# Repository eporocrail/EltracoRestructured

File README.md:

Aim is to develop a switching and signaling system for model railroad track control.
  Communication is wireless.

  To disconnect the decoder from the controlling software in space and time the MOSQUITTO
  MQTT broker is used.

  Hardware setup is as simple as possible. In stead of having one hardware module for diffferent applications
  the design aims for three different PCB's specific to task where the Wemos has to be slotted into.

  Sofware is modularised. It is gathered into one software package. The functionality of each separate decoder
  is configured by means of a website genrated by the decoder.

  *********************************************************************************************

  Target platform is Wemos D1 mini.

  11 digital input/output pins, all pins have interrupt/pwm/I2C/one-wire supported(except D0)
  1 analog input(3.2V max input)
  a Micro USB connection
  compatible with Arduino IDE.
  pins are active LOW but the Arduino IDE inverts this.

  All of the IO pins run at 3.3V:
  A levelshifter or voltage divider is required.

  For a relay a pin is followed by a transistor/IC. A relay is driven with 5V.

  For a sensor or servo each pin is followed by a 330R resistor to limit current to 10 mA.

  eltraco decoder     Function

  eltraco sensor decoder    Scanning 9 sensors
  eltraco switch decoder    Controlling 8 outputs
  eltraco turnout decoder   Controlling 2 turnouts

  GPIO usage:

  Decoder  pins     function

  Sensor   D0 .. D7     digital sensor
  
           A0           analogue sensor

  Switch   D0 .. D7     output (switch)

  Double   D0    relais 1
  
  Turnout  D1    current detector 1
           
           D2    current detector 2
           
           D3    not used
           
           D4    not used
           
           D5    relais 2
           
           D6    servo 1
           
           D7    servo 2
           
           D8    not used
           
           A0    not used
           
  Single   D0    relais 1
  
  Turnout  D1    current detector 1
           
           D2    sensor
           
           D3    sensor
           
           D4    sensor
           
           D5    sensor
           
           D6    servo 1
           
           D7    not used
           
           D8    not used
           
           A0    not used         

  ROCNET PROTOCOL

  packet payload content:
  byte 1  : groupId
  
  byte 2  : receiveIdH
  
  byte 3  : receiveIdL
  
  byte 4  : sendIdH
  
  byte 5  : sendIdL
  
  byte 6  : group
  
  byte 7  : code
  
  byte 8  : length
  
  byte 9  : data1
  
  byte 10 : data2
  
  byte 11 : data3
  
  byte 12 : data4

  --byte 1 only used for large network. Normally 0.

  --byte 2 only used when more than 255 decoders. Normally 0.

  --byte 3 Rocrail Server default Id is 1

  Broadcast Id = 0
  
  Decoder   Id = 2 ... 255   Not used for switching decoder

  --byte 4 only used when more than 255 decoders. Normally 0.

  --byte 5 Rocrail Server default Id is 1

  Decoder Id   = 2 ... 255 with restrictions as described under "addressing"

  --byte 6

  groups
  code   description     remark                     MQTT topic
  
  0      Host            Rocrail                    rocnet/ht
  
  7      Clock Fast      Clock                      rocnet/ck
  
  8      Sensor          Position determination     rocnet/sr
  
  9      Output                                     rocnet/ot

  --byte 7

  Code:  bit 7 = 0
  
     bit 6 and bit 5 represent Type of code
     
     bit 4 .. 0:  5 bit command 0 .. 31

  Type: 0 - test
  
  1 - request
  
  2 - event
  
  3 - reply

  Sensor

  Actions
  code description data 1  data 2  data 3  data 4  data n
  1    report      addrH¹  addrL¹  status  port    identifier (RFID)

  ¹) Address of the reporting loco.
  The sensor ID is set in the header; Sender.

  Output

  Type   Value
  
  switch   0
  
  light    1
  
  servo    2

  Actions
  code description data 1  data 2  data 3
  
  0      off       type    value   address
  
  1      on        type    value   address

  --byte 8 Netto number of following data bytes.

  At a speed of 200 KmH a loc runs 64 mm per second in scale H0 and 35 mm per second in scale N.
  To come to a reliable detection reaction a point sensor must be scanned at least 20 times per second in H0
  and at least 10 times per second in scale N.

  For scale H0 scan delay should be not larger than 50 miliseconds and for scale N not larger
  than 100 miliseconds. Default will be 20.

  The Wemos Module needs no 3.3V power supply. To the 5V pin external powersupply can be connected.

  Addressing:

  Addressing falls apart in a WiFi address, being an IP-address and a Rocnet address.

  Rocnet:

  In the Rocnet protocol (IdH*256 + IdL) represents the Rocnet Node Number. This number ranges from 1 .. 65536.
  It represents the "Bus" number.
  Depending on the function performed the I/O pin of the decoder is addressed with "data3" for
  "output" functions or "data4" for "sensor" functions. Turnouts are controlled with an "output" function.
  The values of data3/data4 are in rocrail inserted in field "Address"

  For eltraco an I/O pin is addressed by the combination of receiveIdL and data3/data4.
  This way each individual pin of each individual decoder can be addressed.

  A second way to address an IO pin is using a "fixed" receiveIdL and discriminating by means of data3/data4.
  Using this method provides in eltraco the possibility to address 255 turnouts by a consecutive number only.
  The default receiveIdL of Rocrail is "9". This receiveIdL is used to control turnouts. These addresses are
  used by the servo-tool to adjust the servo of a turnout.

  IP-address:
  The following IP-adress range is available:
  192.168.xxx.xxx

  IP-addres: Router 192.168.xxx.251
  
             Configuration website 192.168.xxx.252
             
             Command Station       192.168.xxx.253
             
             Mosquitto             192.168.xxx.254

  For the decoders are available 192.168.xxx.2 - 192.168.2.250

  Each decoder is allocated a unique IP-address out of the range 192.168.xxx.2 - 192.168.2.250.
  The last triplet is the Rocrail "Bus" number.

  Single turnout decoder:

Each decoder controls 1 turnout and reports occupation of it.

For the turnout decoder occupation of the turnout is reported at "Address" 1.

Table: Switches tab Interface - the last part of the IP-address is inserted into field "Bus"
       "1" is inserted into field "Address".
       e.g. (192.168.0.154 turnout is inserted as Bus 154 Address 1)

Table: Sensor tab Interface - the last part of the IP-address is inserted into field "Bus"
       "1" is inserted into field "Address". The external sensors report using "Address" numbers 2 .. 5.
       e.g. (192.168.0.154 turnout is inserted as Bus 154 Address 1, the second external sensor of the same
       decoder is inserted as Bus 154 Address 3)

Double turnout decoder:

Each decoder controls 2 turnouts and reports occupation of them.

For the turnout decoder occupation of the first turnout is reported at "Address" 1 and of the second
turnout at "Address" 2.

Table: Switches tab Interface - the last part of the IP-address is inserted into field "Bus"
       For the first turnout "1" is inserted into field "Address". For the second one "2" is inserted
       e.g. (192.168.0.154 turnout 2 is inserted as Bus 154 Address 2)

Table: Sensor tab Interface - the last part of the IP-address is inserted into field "Bus"
       For the first turnout "1" is inserted into field "Address". For the second one "2" is inserted
       e.g. (192.168.0.154 turnout 2 is inserted as Bus 154 Address 2)

Operation

During testing it turned out that move orders from Rocrail arrived so fast that an ongoing movement was
interrupted. To cater for this, incoming turnout orders are stored into a buffer. When ongoing movement is concluded,
buffer content is converted into a turnout order and the next turnout starts moving.

Sensor decoder:
Each decoder has eight digital and one analogue sensor.

The sensors report using "Address" numbers 1 .. 9.
Use of the analogue sensor is to be programmed by the user.

Table: Sensor tab Interface - the last part of the IP-address is inserted into field "Bus"
       port number is inserted into field "Address"
       e.g. (192.168.0.076 sensor 5 is inserted as Bus 76 Address 5)

Operation

The state of the sensor is controlled by interrupt. Not only the state of the sensor but also the point in time of activation is stored.
If the sensor is still in the activated state after the debounce period has passed the Sensor Message is sent. 

The state of the sensor will change to "inactive" by interrupt. After the minimum activation time has passed this inactive state is signalled 

The state of the sensor will change to "inactive" by interrupt. After the minimum activation counts has passed this inactive state is signalled 

with a Sensor Message.

Interrupt reacts on changes to drive the sensor state.

D0 can NOT be used with Interrupt. This reduces the amount of interrupt driven sensors per module to 7. (D1 .. D7).

D0 has to be watched with "polling".

Switch decoder
Each decoder has eight outputs.

Each decoder is allocated a unique IP-address out of the range 192.168.xxx.2 - 192.168.2.250.
The last triplet is the Rocrail "Bus" number.

The outputs are switched using "Address" numbers 1 .. 8.

Table: Switches tab Interface - the last part of the IP-address is inserted into field "Bus"
       The individual port number is inserted into field "Address"
       e.g. (192.168.0.201 port 3 is inserted as Bus 201 Address 3)

Operation

Via configuration it is possible to have an output switched ON during 200 mSec. An additional relais attached to that
output can be used to control a solenoid activated device.

To signal the state of a switch, a sensor message is transmitted after each switch action. 

Configuration of decoder

The Wemos module can be used in "ST" mode and "AP" mode simultaneously.
In "ST" mode it is possible to login onto an existing WiFi network for normal operations.
In "AP" mode it is possible to generate its own WiFi network. This network is used for configuration of the decoder.
Each module has its own configuration webserver on a shared WiFi configuration network with its own IP address.

The websever is based on the "EmbAJAX" library. This library facilitates dataexchange between webserver on the decoder
and a browser on a client. The user experience is as much as possible comparable with webservers on PC like hardware.

Configuration data and servo angles are stored in EEPROM.
Allocation of EEPROM memory to variables has to be planned.
  location variable
      0    AngleA1
      1    AngleB1
      2    Delay1
      3    Swap1
      4    AngleA2
      5    AngleB2
      6    Delay2
      7    Swap2
      8    decoderType
      9    debugFlag

  GENERALOFFSET+ 0 .. 25 ST WiFi SSID
  
  GENERALOFFSET + SSIDOFFSET + 0 .. 8 ST WiFi Password
  
  GENERALOFFSET + SSIDOFFSET + PWDOFFSET + 0 .. 6 ST WiFi IP address triplets
  
  GENERALOFFSET + SSIDOFFSET + PWDOFFSET + IPOFFSET + 0 .. 8 Output puls 
  
  GENERALOFFSET + SSIDOFFSET + PWDOFFSET + IPOFFSET + OUTPUTOFFSET + 0 .. 8 Switch active puls length

Configuration data and servo angles are stored in EEPROM.
Allocation of EEPROM memory to variables has to be planned.
  location variable
      0    AngleA1
      1    AngleB1
      2    Delay1
      3 .  Swap1
      4    AngleA2
      5    AngleB2
      6    Delay2
      7 .  Swap2
      8    decoderType
      9    debugFlag

  GENERALOFFSET+ 0 .. 25 ST WiFi SSID
  
  GENERALOFFSET + SSIDOFFSET + 0 .. 8 ST WiFi Password
  
  GENERALOFFSET + SSIDOFFSET + PWDOFFSET `+ 0 .. 6 ST WiFi IP address triplets
  
  GENERALOFFSET + SSIDOFFSET + PWDOFFSET + IPOFFSET + 0 .. 8 Output puls 
  
  GENERALOFFSET + SSIDOFFSET + PWDOFFSET + IPOFFSET + OUTPUTOFFSET + 0 .. 8 Switch active puls length 
  
  GENERALOFFSET + SSIDOFFSET + PWDOFFSET + IPOFFSET + OUTPUTOFFSET + PULSLENGTHOFFSET+ 0 .. 8 Output sensor message

  GENERALOFFSET      - 20
  SSIDOFFSET         - 30
  PWDOFFSET          - 20
  IPOFFSET           - 10
  OUTPUTOFFSET        -10
  PULSLENGTHOFFSET    -20
  OUTPUTSENSOROFFSET  -10

The ST WiFi password is generated out of "ELTRACO" and the decoderId.
The AP WiFi SSID is generated out of "ELTRACO" and the decoderID. This also aplies to the related password.

There are two ways to transfer Software to the decoder.
Via USB cable and after inital software installation also "Over The Air"(OTA).
Each decoder has its own OTA name which is generated outof "ELTRACO" and the decoderId.

Author: E. Postma

November 2018

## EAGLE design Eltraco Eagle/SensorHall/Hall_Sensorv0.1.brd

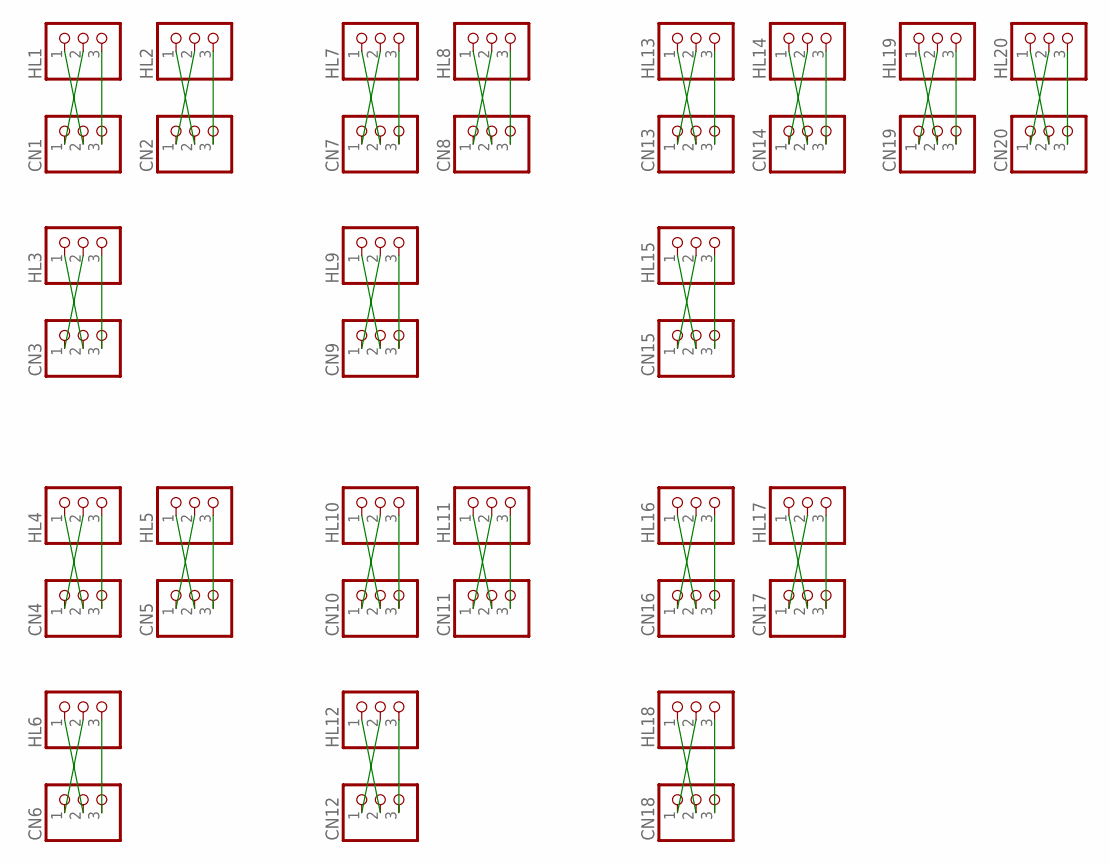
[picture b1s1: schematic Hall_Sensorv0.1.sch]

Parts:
CN1, CN2, CN3, CN4, CN5, CN6, CN7, CN8, CN9, CN10, CN11, CN12, CN13, CN14, CN15, CN16, CN17, CN18, CN19, CN20: PINHD-1X3; 1X03
HL1, HL2, HL3, HL4, HL5, HL6, HL7, HL8, HL9, HL10, HL11, HL12, HL13, HL14, HL15, HL16, HL17, HL18, HL19, HL20: PINHD-1X3; 1X03

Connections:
unnamed: CN1.1, HL1.2
unnamed: CN1.2, HL1.1
unnamed: CN7.3, HL7.3
unnamed: CN2.2, HL2.1
unnamed: CN2.1, HL2.2
unnamed: CN8.3, HL8.3
unnamed: CN7.2, HL7.1
unnamed: CN7.1, HL7.2
unnamed: CN9.3, HL9.3
unnamed: CN8.2, HL8.1
unnamed: CN8.1, HL8.2
unnamed: CN10.3, HL10.3
unnamed: CN13.2, HL13.1
unnamed: CN13.1, HL13.2
unnamed: CN11.3, HL11.3
unnamed: CN14.2, HL14.1
unnamed: CN14.1, HL14.2
unnamed: CN12.3, HL12.3
unnamed: CN19.2, HL19.1
unnamed: CN19.1, HL19.2
unnamed: CN13.3, HL13.3
unnamed: CN20.2, HL20.1
unnamed: CN20.1, HL20.2
unnamed: CN14.3, HL14.3
unnamed: CN15.2, HL15.1
unnamed: CN15.1, HL15.2
unnamed: CN15.3, HL15.3
unnamed: CN9.2, HL9.1
unnamed: CN9.1, HL9.2
unnamed: CN16.3, HL16.3
unnamed: CN3.2, HL3.1
unnamed: CN3.1, HL3.2
unnamed: CN17.3, HL17.3
unnamed: CN4.2, HL4.1
unnamed: CN4.1, HL4.2
unnamed: CN18.3, HL18.3
unnamed: CN5.2, HL5.1
unnamed: CN5.1, HL5.2
unnamed: CN19.3, HL19.3
unnamed: CN10.2, HL10.1
unnamed: CN10.1, HL10.2
unnamed: CN11.2, HL11.1
unnamed: CN20.3, HL20.3
unnamed: CN11.1, HL11.2
unnamed: CN1.3, HL1.3
unnamed: CN16.2, HL16.1
unnamed: CN16.1, HL16.2
unnamed: CN17.2, HL17.1
unnamed: CN17.1, HL17.2
unnamed: CN6.2, HL6.1
unnamed: CN2.3, HL2.3
unnamed: CN6.1, HL6.2
unnamed: CN12.2, HL12.1
unnamed: CN12.1, HL12.2
unnamed: CN3.3, HL3.3
unnamed: CN18.2, HL18.1
unnamed: CN18.1, HL18.2
unnamed: CN4.3, HL4.3
unnamed: CN5.3, HL5.3
unnamed: CN6.3, HL6.3

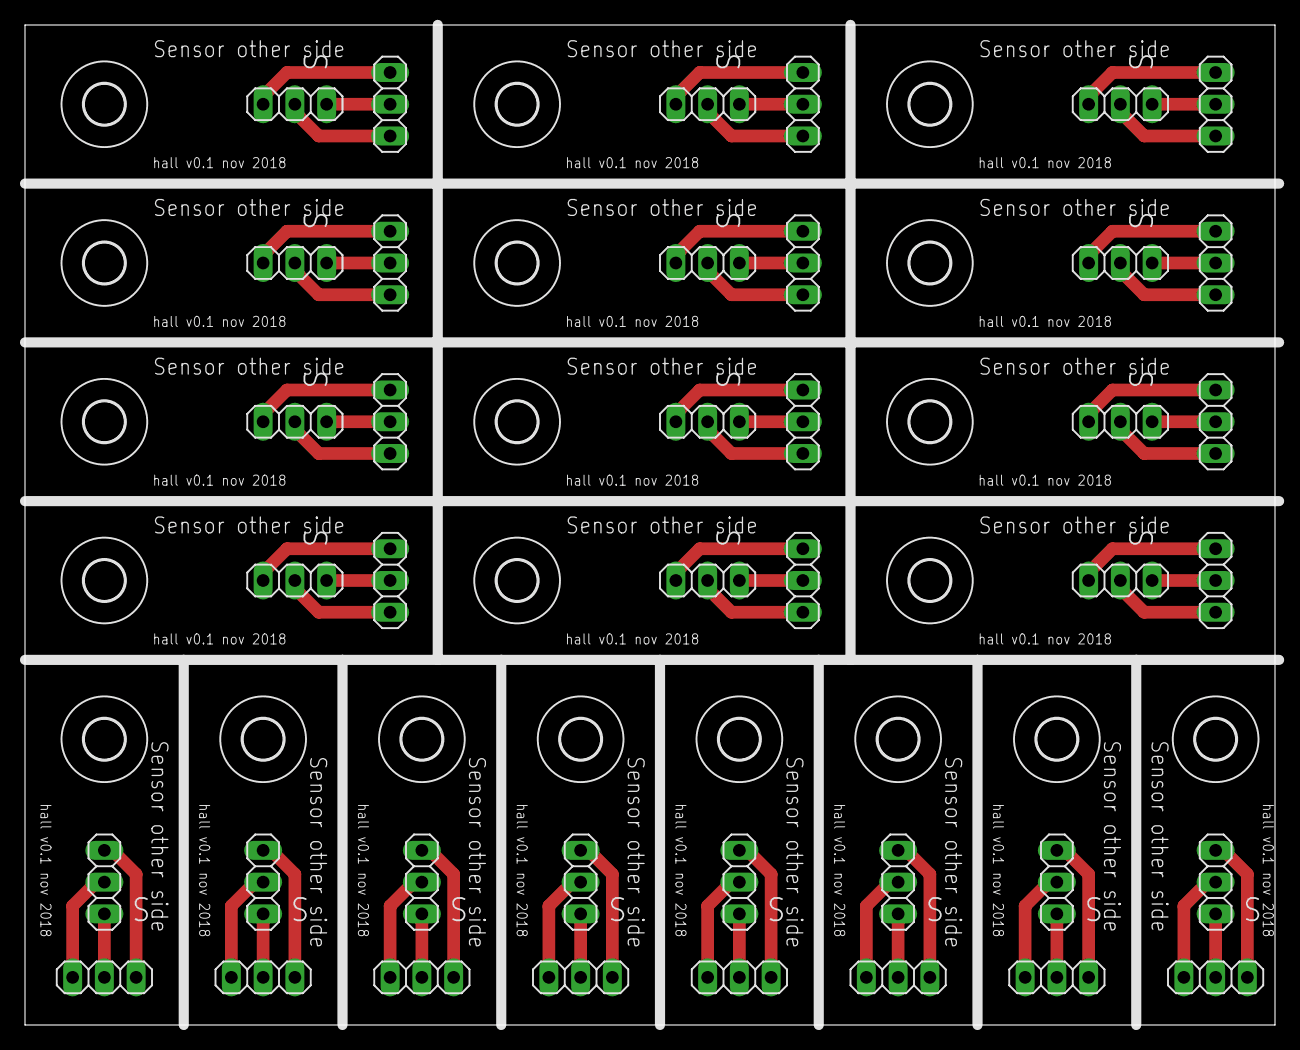
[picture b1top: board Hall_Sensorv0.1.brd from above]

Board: 2 copper layers, 100.0 x 80.0 mm, 60 parts (0 on the bottom side), 60 nets.

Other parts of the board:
U$1, U$2, U$3, U$4, U$5, U$6, U$7, U$8, U$9, U$10, U$11, U$12, U$13, U$14, U$15, U$16, U$17, U$18, U$19, U$20: 3,2

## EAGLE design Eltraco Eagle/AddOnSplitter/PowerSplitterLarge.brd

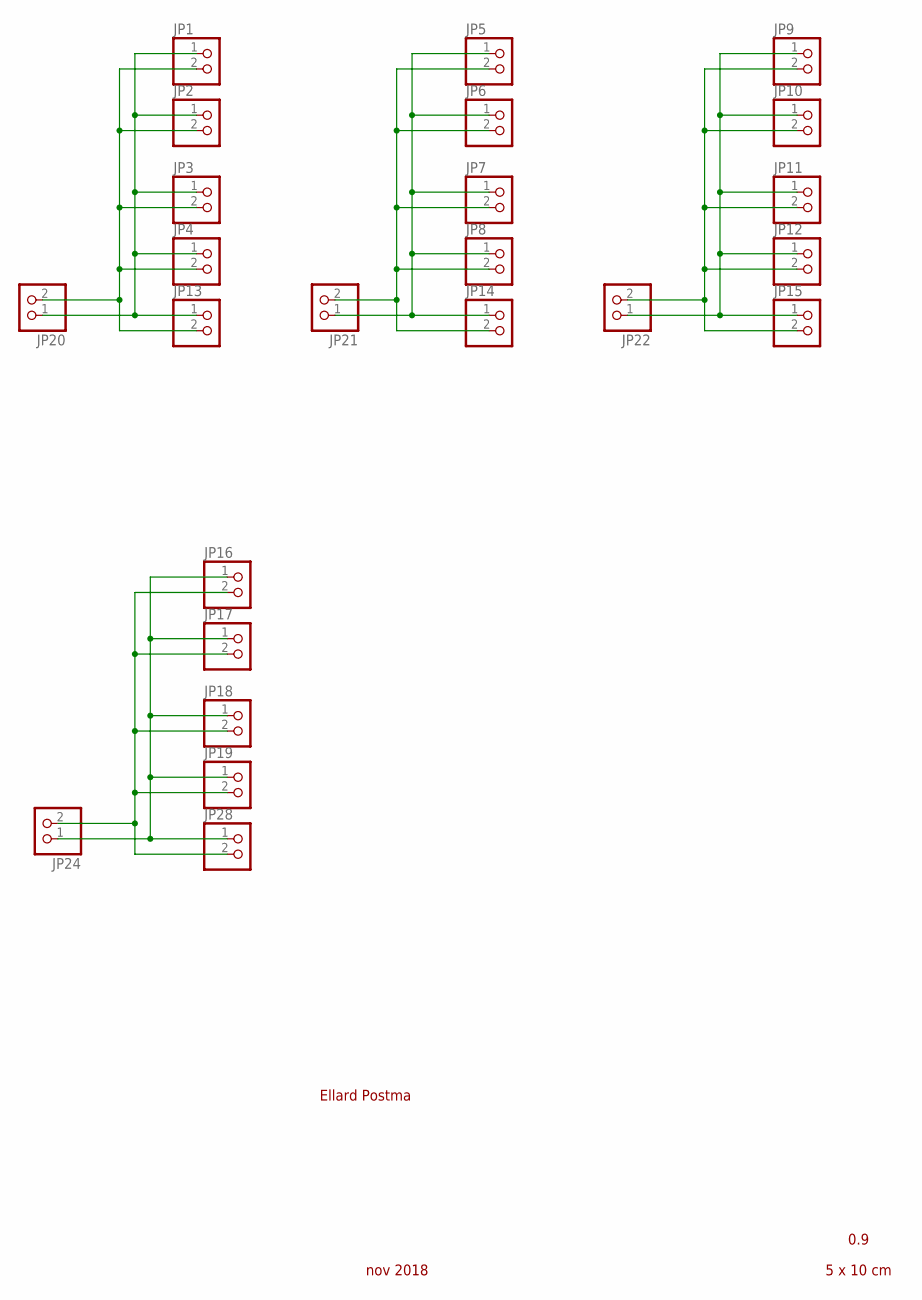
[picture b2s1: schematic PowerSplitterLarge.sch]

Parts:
JP1, JP2, JP3, JP4, JP5, JP6, JP7, JP8, JP9, JP10, JP11, JP12, JP13, JP14, JP15, JP16, JP17, JP18, JP19, JP20, JP21, JP22, JP24, JP28: PINHD-1X2/90; 1X02/90

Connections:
G1: JP1.2, JP2.2, JP3.2, JP4.2, JP13.2, JP20.2
G2: JP5.2, JP6.2, JP7.2, JP8.2, JP14.2, JP21.2
G3: JP9.2, JP10.2, JP11.2, JP12.2, JP15.2, JP22.2
G4: JP16.2, JP17.2, JP18.2, JP19.2, JP24.2, JP28.2
PLUS: JP1.1, JP2.1, JP3.1, JP4.1, JP13.1, JP20.1
PLUS2: JP5.1, JP6.1, JP7.1, JP8.1, JP14.1, JP21.1
PLUS3: JP9.1, JP10.1, JP11.1, JP12.1, JP15.1, JP22.1
PLUS4: JP16.1, JP17.1, JP18.1, JP19.1, JP24.1, JP28.1

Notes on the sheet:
Ellard Postma
nov 2018
5 x 10 cm
0.9

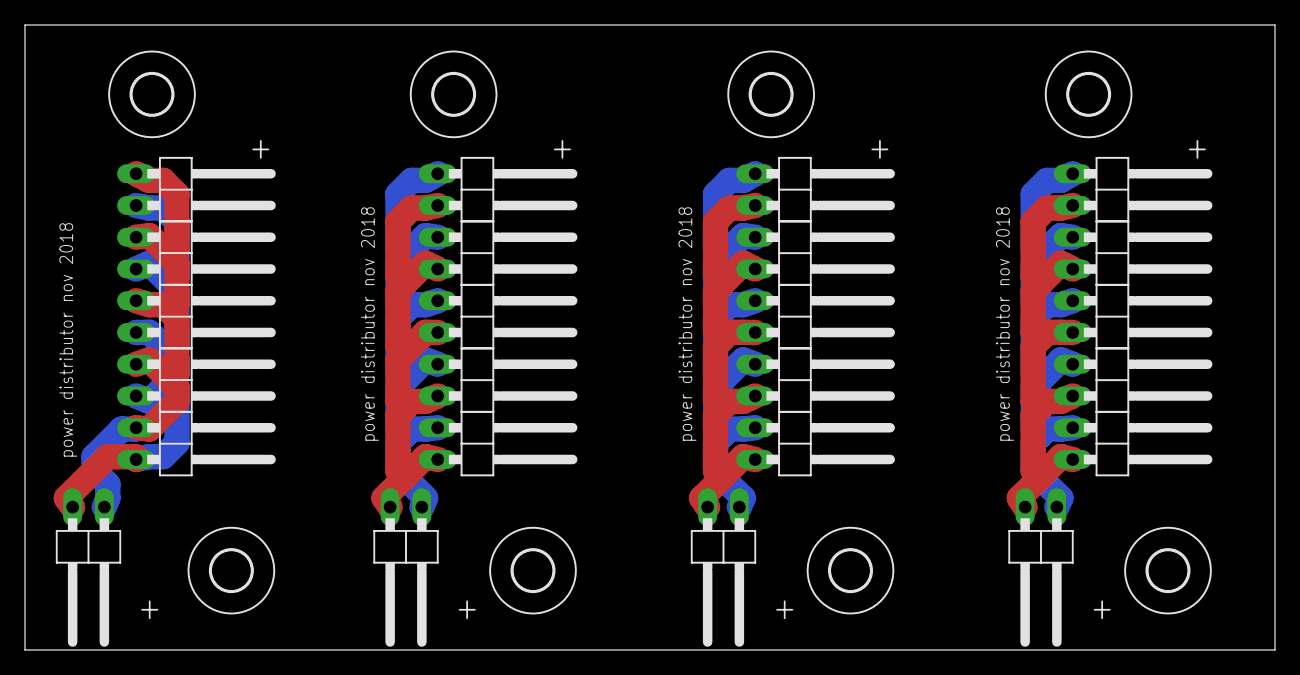
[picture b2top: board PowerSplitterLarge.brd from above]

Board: 2 copper layers, 100.0 x 50.0 mm, 32 parts (0 on the bottom side), 8 nets.

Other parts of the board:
U$1, U$2, U$3, U$4, U$5, U$6, U$7, U$8: 3,2

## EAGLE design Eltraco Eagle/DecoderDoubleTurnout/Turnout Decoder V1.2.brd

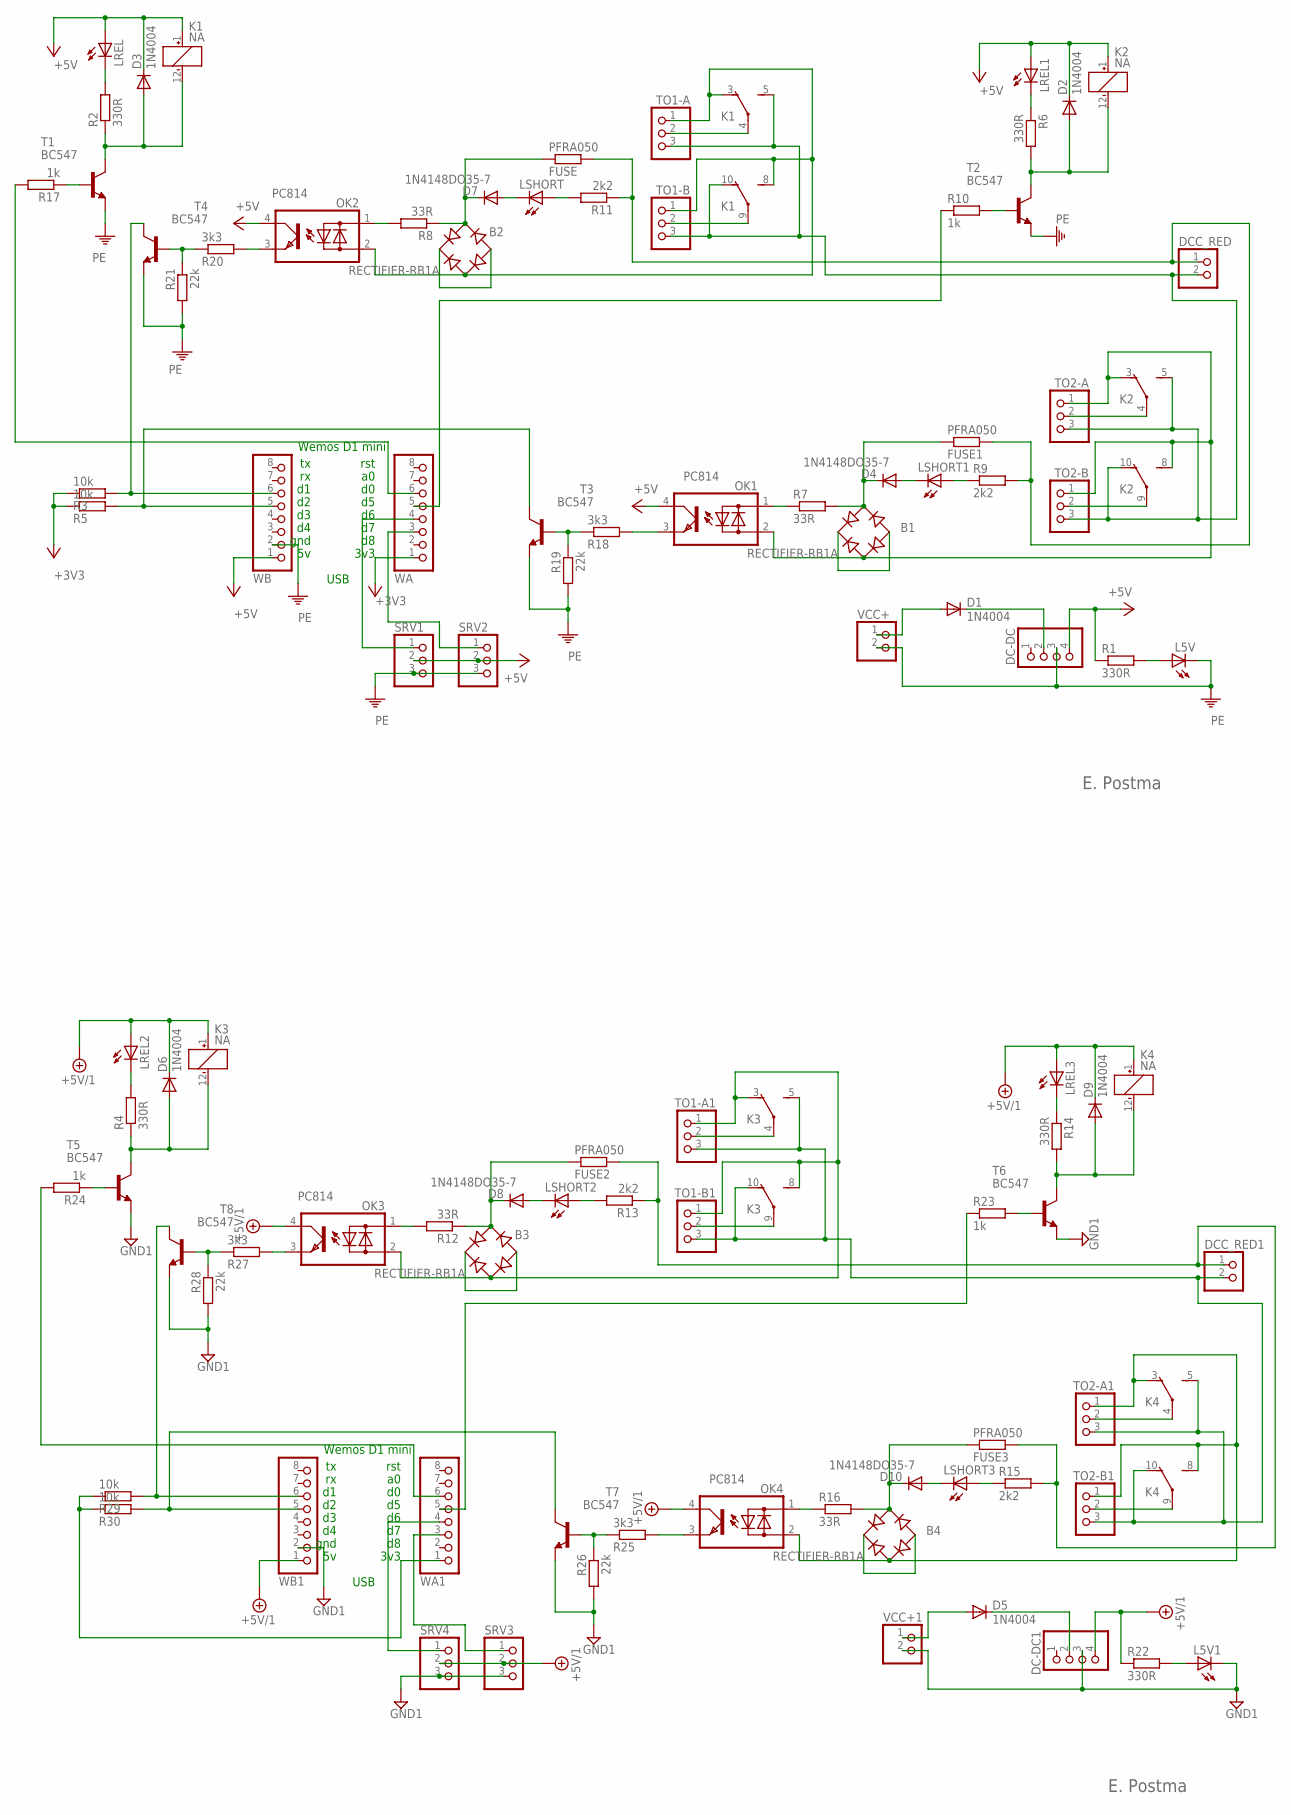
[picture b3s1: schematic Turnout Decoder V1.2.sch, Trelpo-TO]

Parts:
B1, B2, B3, B4: RECTIFIER-RB1A; RB1A
D1, D2, D3, D5, D6, D9: 1N4004; DO41-10
D4, D7, D8, D10: 1N4148DO35-7; DO35-7
DC-DC, DC-DC1: PINHD-1X4; 1X04
DCC_RED, DCC_RED1: PINHD-1X2; 1X02
FUSE, FUSE1, FUSE2, FUSE3: PFRA050; 0414V
K1, K2, K3, K4: NA
L5V, L5V1: LED3MM
LREL, LREL1, LREL2, LREL3: LED3MM
LSHORT, LSHORT1, LSHORT2, LSHORT3: LED3MM
OK1, OK2, OK3, OK4: PC814; DIL04
R1, R2, R4, R6, R14, R22: 330R; 0207/7
R3, R5, R29, R30: 10k; 0207/7
R7, R8, R12, R16: 33R; 0207/7
R9, R11, R13, R15: 2k2; 0207/7
R10, R17, R23, R24: 1k; 0207/7
R18, R20, R25, R27: 3k3; 0207/7
R19, R21, R26, R28: 22k; 0207/7
SRV1, SRV2, SRV3, SRV4: PINHD-1X3; 1X03
T1, T2, T3, T4, T5, T6, T7, T8: BC547; TO92
TO1-A, TO1-A1, TO1-B, TO1-B1, TO2-A, TO2-A1, TO2-B, TO2-B1: PINHD-1X3; 1X03
VCC+, VCC+1: PINHD-1X2; 1X02
WA, WA1: PINHD-1X8; 1X08
WB, WB1: PINHD-1X8; 1X08

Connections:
+3V3: R3.1, R5.1, WA.1
+5V: D2.C, D3.C, DC-DC.4, K1.1 (+), K2.1 (+), LREL.A, LREL1.A, OK1.4 (C), OK2.4 (C), R1.1, SRV1.2, SRV2.2, WB.1
+5V/1: D6.C, D9.C, DC-DC1.4, K3.1 (+), K4.1 (+), LREL2.A, LREL3.A, OK3.4 (C), OK4.4 (C), R22.1, SRV3.2, SRV4.2, WB1.1
GND1: DC-DC1.3, L5V1.K (C), R26.2, R28.2, SRV3.3, SRV4.3, T5.1 (E), T6.1 (E), T7.1 (E), T8.1 (E), VCC+1.2, WB1.2
unnamed: LREL2.K (C), R4.2
unnamed: LREL1.K (C), R6.1
unnamed: DCC_RED.1, FUSE.2, FUSE1.2, R9.2, R11.1
unnamed: D1.A, VCC+.1
unnamed: OK1.1 (AC1), R7.1
unnamed: LSHORT1.A, R9.1
unnamed: D4.A, LSHORT1.K (C)
unnamed: D2.A, K2.12 (-), R6.2, T2.3 (C)
unnamed: R10.2, T2.2 (B)
unnamed: B1.+, B1.-
unnamed: OK1.3 (E), R18.2
unnamed: LREL.K (C), R2.2
unnamed: K2.4, TO2-A.2
unnamed: B2.AC2, K1.3 (O), K1.8 (S), OK2.2 (AC2), TO1-A.1, TO1-B.1
unnamed: K2.9, TO2-B.2
unnamed: DCC_RED.2, K1.5 (S), K1.10 (O), K2.5 (S), K2.10 (O), TO1-A.3, TO1-B.3, TO2-A.3, TO2-B.3
unnamed: OK2.3 (E), R20.2
unnamed: B1.AC2, K2.3 (O), K2.8 (S), OK1.2 (AC2), TO2-A.1, TO2-B.1
unnamed: R3.2, T4.3 (C), WB.6
unnamed: B1.AC1, D4.C, FUSE1.1, R7.2
unnamed: OK2.1 (AC1), R8.2
unnamed: R5.2, T3.3 (C), WB.5
unnamed: B2.AC1, D7.C, FUSE.1, R8.1
unnamed: OK3.1 (AC1), R12.2
unnamed: LSHORT2.A, R13.2
unnamed: K1.4, TO1-A.2
unnamed: R18.1, R19.1, T3.2 (B)
unnamed: R20.1, R21.1, T4.2 (B)
unnamed: R17.2, WA.6
unnamed: D8.A, LSHORT2.K (C)
unnamed: SRV1.1, WA.4
unnamed: K1.9, TO1-B.2
unnamed: SRV2.1, WA.3
unnamed: R10.1, WA.5
unnamed: LSHORT.A, R11.2
unnamed: D6.A, K3.12 (-), R4.1, T5.3 (C)
unnamed: R24.1, T5.2 (B)
unnamed: B3.+, B3.-
unnamed: L5V1.A, R22.2
unnamed: D5.A, VCC+1.1
unnamed: D7.A, LSHORT.K (C)
unnamed: B2.+, B2.-
unnamed: D5.C, DC-DC1.2
unnamed: K3.4, TO1-A1.2
unnamed: K3.9, TO1-B1.2
unnamed: L5V.A, R1.2
unnamed: B3.AC2, K3.3 (O), K3.8 (S), OK3.2 (AC2), TO1-A1.1, TO1-B1.1
unnamed: B3.AC1, D8.C, FUSE2.1, R12.1
unnamed: R17.1, T1.2 (B)
unnamed: D3.A, K1.12 (-), R2.1, T1.3 (C)
unnamed: LREL3.K (C), R14.1
unnamed: OK4.1 (AC1), R16.1
unnamed: LSHORT3.A, R15.1
unnamed: D10.A, LSHORT3.K (C)
unnamed: D9.A, K4.12 (-), R14.2, T6.3 (C)
unnamed: R23.2, T6.2 (B)
unnamed: B4.+, B4.-
unnamed: D1.C, DC-DC.2
unnamed: K4.4, TO2-A1.2
unnamed: K4.9, TO2-B1.2
unnamed: DCC_RED1.2, K3.5 (S), K3.10 (O), K4.5 (S), K4.10 (O), TO1-A1.3, TO1-B1.3, TO2-A1.3, TO2-B1.3
unnamed: B4.AC2, K4.3 (O), K4.8 (S), OK4.2 (AC2), TO2-A1.1, TO2-B1.1
unnamed: B4.AC1, D10.C, FUSE3.1, R16.2
unnamed: DCC_RED1.1, FUSE2.2, FUSE3.2, R13.1, R15.2
unnamed: SRV3.1, WA1.3
unnamed: R23.1, WA1.5
unnamed: SRV4.1, WA1.4
unnamed: R25.1, R26.1, T7.2 (B)
unnamed: R27.1, R28.1, T8.2 (B)
unnamed: R24.2, WA1.6
unnamed: R29.2, T8.3 (C), WB1.6
unnamed: OK3.3 (E), R27.2
unnamed: OK4.3 (E), R25.2
unnamed: R30.2, T7.3 (C), WB1.5
unnamed: R29.1, R30.1, WA1.1
PE: DC-DC.3, L5V.K (C), R19.2, R21.2, SRV1.3, SRV2.3, T1.1 (E), T2.1 (E), T3.1 (E), T4.1 (E), VCC+.2, WB.2

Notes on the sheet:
rst
3v3
Wemos D1 mini
gnd
USB
E. Postma

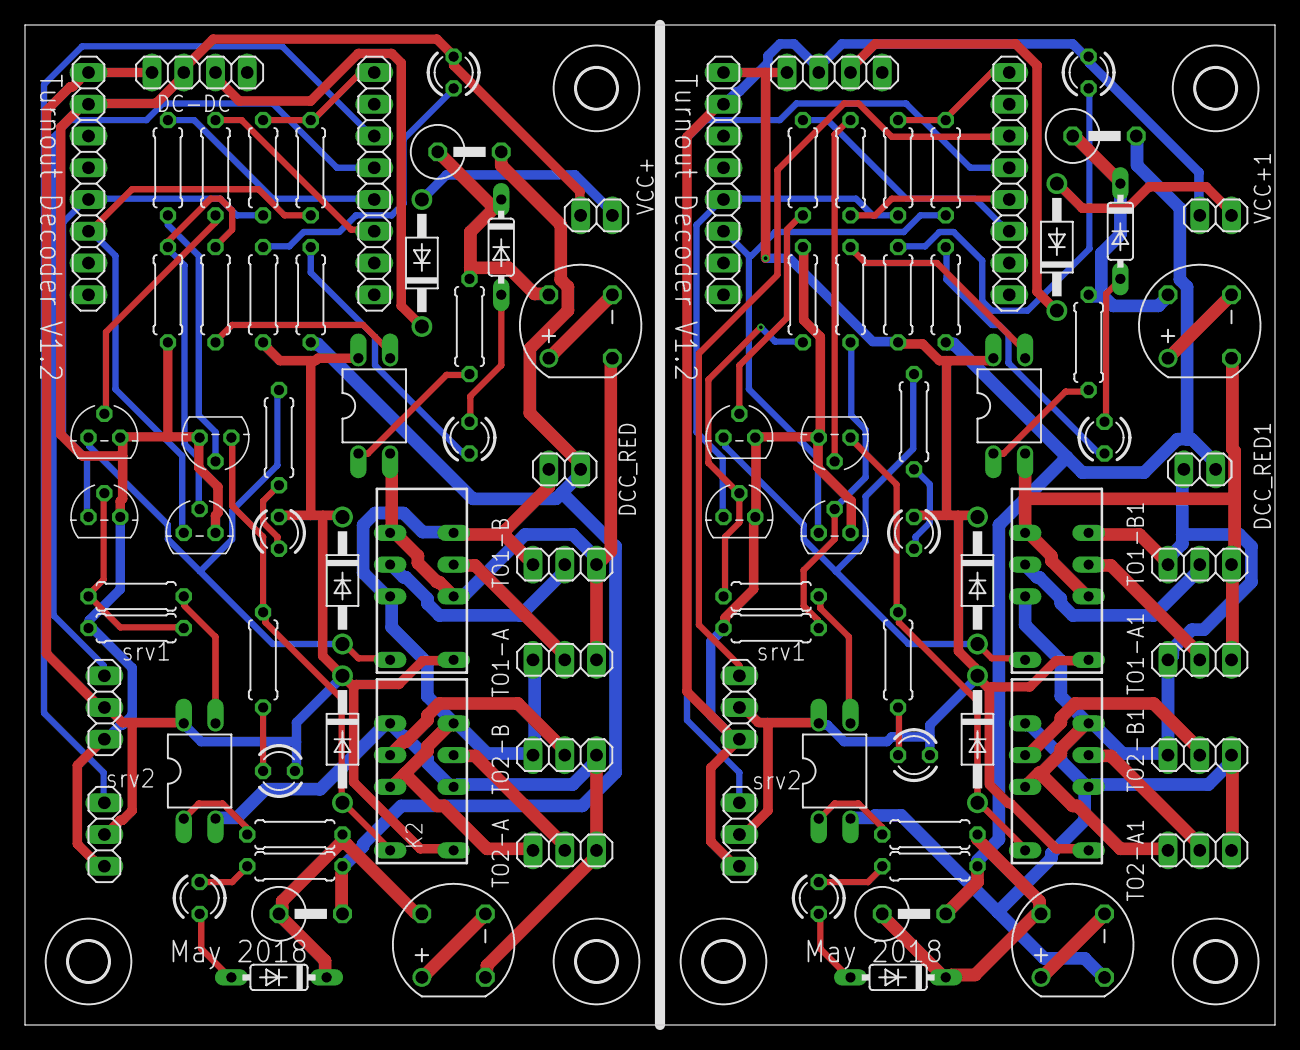
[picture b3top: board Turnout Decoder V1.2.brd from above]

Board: 2 copper layers, 100.0 x 80.0 mm, 102 parts (0 on the bottom side), 80 nets.

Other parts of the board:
U$1, U$2, U$3, U$4, U$5, U$6: 3,2

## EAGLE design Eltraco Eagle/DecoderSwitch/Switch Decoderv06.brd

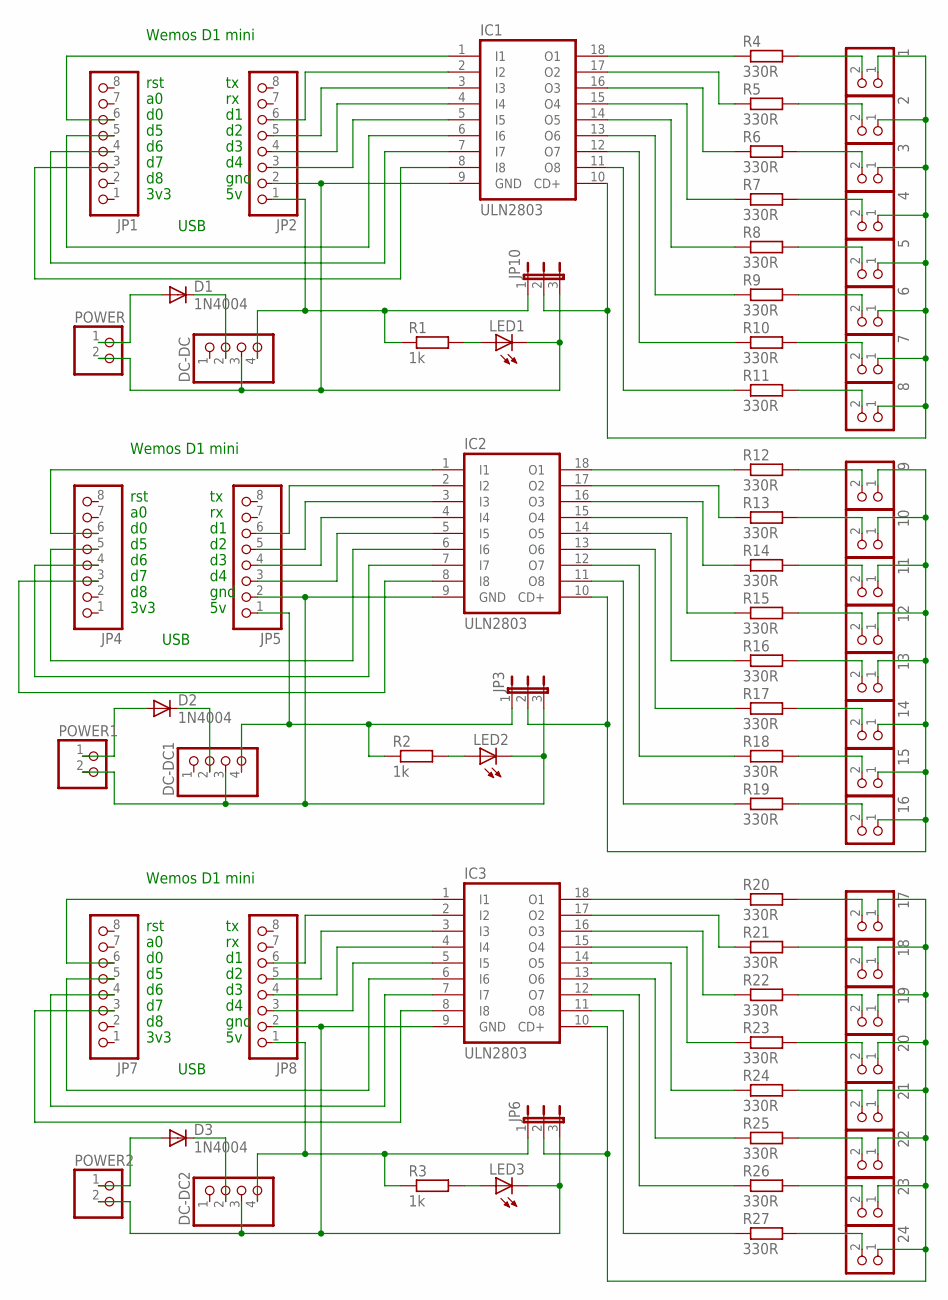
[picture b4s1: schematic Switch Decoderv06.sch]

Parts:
1, 2, 3, 4, 5, 6, 7, 8, 9, 10, 11, 12, 13, 14, 15, 16, 17, 18, 19, 20, 21, 22, 23, 24: PINHD-1X2; 1X02
D1, D2, D3: 1N4004; DO41-10
DC-DC, DC-DC1, DC-DC2: PINHD-1X4; 1X04
IC1, IC2, IC3: ULN2803; DIL18
JP1, JP2, JP4, JP5, JP7, JP8: PINHD-1X8; 1X08
JP3, JP6, JP10: JP2E; JP2
LED1, LED2, LED3: LED3MM
POWER, POWER1, POWER2: PINHD-1X2; 1X02
R1, R2, R3: 1k; 0309/10
R4, R5, R6, R7, R8, R9, R10, R11, R12, R13, R14, R15, R16, R17, R18, R19, R20, R21, R22, R23, R24, R25, R26, R27: 330R; 0207/7

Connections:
unnamed: DC-DC.3, IC1.9 (GND), JP2.2, JP10.3, LED1.K (C), POWER.2
unnamed: IC1.1 (I1), JP1.6
unnamed: IC1.7 (I7), JP1.4
unnamed: D1.C, DC-DC.2
unnamed: IC1.6 (I6), JP1.5
unnamed: LED1.A, R1.2
unnamed: IC1.3 (I3), JP2.5
unnamed: 1.1, 2.1, 3.1, 4.1, 5.1, 6.1, 7.1, 8.1, IC1.10 (CD+), JP10.2
unnamed: IC1.5 (I5), JP2.3
unnamed: IC1.2 (I2), JP2.6
unnamed: IC1.8 (I8), JP1.3
unnamed: IC1.18 (O1), R4.1
unnamed: IC1.4 (I4), JP2.4
unnamed: IC2.1 (I1), JP4.6
unnamed: 1.2, R4.2
unnamed: 9.1, 10.1, 11.1, 12.1, 13.1, 14.1, 15.1, 16.1, IC2.10 (CD+), JP3.2
unnamed: IC1.17 (O2), R5.1
unnamed: 2.2, R5.2
unnamed: 3.2, R6.2
unnamed: IC1.16 (O3), R6.1
unnamed: IC1.15 (O4), R7.1
unnamed: 4.2, R7.2
unnamed: 5.2, R8.2
unnamed: IC1.14 (O5), R8.1
unnamed: IC1.13 (O6), R9.1
unnamed: 6.2, R9.2
unnamed: 7.2, R10.2
unnamed: IC1.12 (O7), R10.1
unnamed: 8.2, R11.2
unnamed: LED2.A, R2.2
unnamed: IC2.2 (I2), JP5.6
unnamed: IC2.3 (I3), JP5.5
unnamed: IC2.4 (I4), JP5.4
unnamed: D2.A, POWER1.1
unnamed: D2.C, DC-DC1.2
unnamed: IC2.5 (I5), JP5.3
unnamed: IC2.6 (I6), JP4.5
unnamed: IC2.7 (I7), JP4.4
unnamed: IC2.8 (I8), JP4.3
unnamed: IC3.18 (O1), R20.1
unnamed: DC-DC1.3, IC2.9 (GND), JP3.3, JP5.2, LED2.K (C), POWER1.2
unnamed: IC1.11 (O8), R11.1
unnamed: IC2.11 (O8), R19.1
unnamed: IC2.18 (O1), R12.1
unnamed: IC2.17 (O2), R13.1
unnamed: 9.2, R12.2
unnamed: D1.A, POWER.1
unnamed: 10.2, R13.2
unnamed: IC2.16 (O3), R14.1
unnamed: IC2.15 (O4), R15.1
unnamed: 11.2, R14.2
unnamed: 12.2, R15.2
unnamed: IC2.14 (O5), R16.1
unnamed: IC2.13 (O6), R17.1
unnamed: 13.2, R16.2
unnamed: 14.2, R17.2
unnamed: IC2.12 (O7), R18.1
unnamed: 15.2, R18.2
unnamed: IC3.1 (I1), JP7.6
unnamed: LED3.A, R3.2
unnamed: IC3.2 (I2), JP8.6
unnamed: IC3.3 (I3), JP8.5
unnamed: IC3.4 (I4), JP8.4
unnamed: D3.A, POWER2.1
unnamed: D3.C, DC-DC2.2
unnamed: IC3.5 (I5), JP8.3
unnamed: IC3.6 (I6), JP7.5
unnamed: IC3.7 (I7), JP7.4
unnamed: IC3.8 (I8), JP7.3
unnamed: 17.1, 18.1, 19.1, 20.1, 21.1, 22.1, 23.1, 24.1, IC3.10 (CD+), JP6.2
unnamed: DC-DC2.3, IC3.9 (GND), JP6.3, JP8.2, LED3.K (C), POWER2.2
unnamed: 16.2, R19.2
unnamed: IC3.11 (O8), R27.1
unnamed: DC-DC.4, JP2.1, JP10.1, R1.1
unnamed: IC3.17 (O2), R21.1
unnamed: DC-DC1.4, JP3.1, JP5.1, R2.1
unnamed: DC-DC2.4, JP6.1, JP8.1, R3.1
unnamed: IC3.16 (O3), R22.1
unnamed: IC3.15 (O4), R23.1
unnamed: 17.2, R20.2
unnamed: IC3.14 (O5), R24.1
unnamed: IC3.13 (O6), R25.1
unnamed: 18.2, R21.2
unnamed: 19.2, R22.2
unnamed: IC3.12 (O7), R26.1
unnamed: 20.2, R23.2
unnamed: 21.2, R24.2
unnamed: 22.2, R25.2
unnamed: 23.2, R26.2
unnamed: 24.2, R27.2

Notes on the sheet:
rst
3v3
Wemos D1 mini
gnd
USB

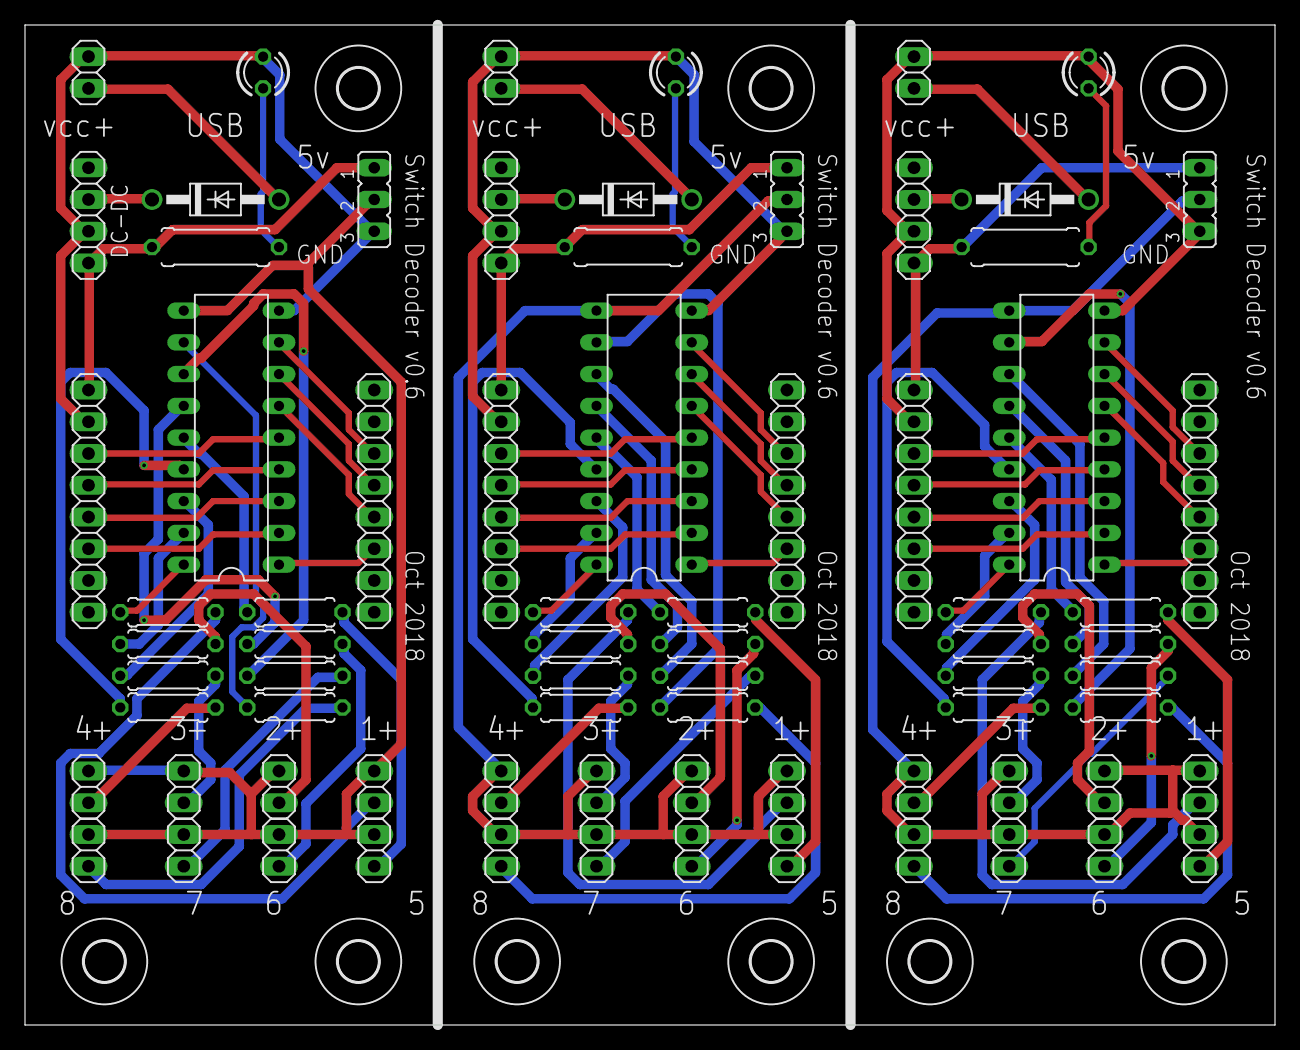
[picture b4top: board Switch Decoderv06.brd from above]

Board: 2 copper layers, 100.0 x 80.0 mm, 84 parts (0 on the bottom side), 90 nets.

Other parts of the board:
U$1, U$2, U$3, U$4, U$5, U$6, U$7, U$8, U$9: 3,2
